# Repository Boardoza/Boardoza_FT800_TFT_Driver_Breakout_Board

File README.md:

# Boardoza FT800 TFT Driver Breakout Board

The **Boardoza FT800 TFT Driver Breakout Board** is a powerful graphics controller solution designed to simplify the creation of high-quality Human-Machine Interfaces (HMIs) for makers and embedded developers. Powered by the **Bridgetek (FTDI) FT800 Embedded Video Engine (EVE)**, this module unburdens your main microcontroller by handling complex graphics rendering, audio processing, and touch control on a dedicated chip. It is the perfect bridge for connecting low-cost MCUs to sophisticated color displays.

Operating with a **5V supply**, the board communicates via a standard **SPI interface** at speeds up to 30 MHz, making it compatible with popular platforms including Arduino, ESP32, STM32, and Raspberry Pi. It supports **WQVGA (480x272)** and **QVGA (320x240)** resolution TFT displays through a standard 40-pin FPC connector. Beyond graphics, it includes a built-in audio engine with PWM output for direct speaker connection. The FT800 offers flexible touch input options with **integrated resistive touch support** and **native capacitive touch connectivity via I²C**, providing a complete multimedia solution for industrial control panels, medical devices, IoT projects, and smart home interfaces.

## [Click here to purchase!](https://www.ozdisan.com/p/arduino-sensorleri-ve-modulleri-613/boardoza-boardoza-ft800-1473939)

|Front Side|Back Side|
|:---:|:---:|
| | |

---

## Key Features

- **Dual Resolution Support:** Compatible with WQVGA (480x272) and QVGA (320x240) TFT panels with both DE mode and VSYNC/HSYNC synchronization.  
- **Works with any MCU:** Uses standard SPI, compatible with Arduino, ESP32, STM32, Raspberry Pi Pico, and more.  
- **Resistive & Capacitive Touch Support:** Integrated resistive and capacitive touch controller support via I²C.  
- **Audio Output:** Mono audio channel with PWM output and dedicated speaker connections.  
- **Object-Oriented Architecture:** Advanced command-based system enables low-cost host MCUs to create sophisticated HMI applications.  
- **Perfect for custom HMIs:** Great for dashboards, robotics screens, measurement devices, smart panels, and DIY UI projects.  
- **Display Control Signals:** Built-in display enable, pixel clock, and sync signal outputs for direct TFT panel control.  
- **Interrupt Capability:** Hardware interrupt output for efficient event-driven programming.  

---

## FT800 vs [FT810](https://github.com/Boardoza/Boardoza_FT810_TFT_Driver_Breakout_Board) Comparison

| Feature | FT800 | [FT810](https://github.com/Boardoza/Boardoza_FT810_TFT_Driver_Breakout_Board) |
|:---|:---:|:---:|
| **Supported Resolutions** | WQVGA (480x272), QVGA (320x240) | up to SVGA (800x600) |
| **Maximum Resolution** | WQVGA (480x272) | SVGA (800x600) |
| **Resistive Touch Support** | ✓ Integrated | ✓ Integrated |
| **Capacitive Touch Support** | ✓ Direct connection via I²C (J9) | ✗ Requires expansion board |
| **Audio Output** | ✓ Mono with PWM output, integrated speaker & line out | ✓ Mono with PWM output, integrated speaker & line out |
| **SPI Interface** | ✓ Up to 30 MHz | ✓ Up to 30 MHz |
| **Board Dimensions** | 40mm x 100mm | 40mm x 100mm |

> **Note:** The FT800 provides native capacitive touch support through the dedicated I²C connector (J9), allowing direct connection to capacitive touch panels. The FT810 focuses on resistive touch integration but can support capacitive touch through an external interface board if needed.

---

## Technical Specifications

**Model:** FT800  
**Manufacturer:** Bridgetek (FTDI)  
**Input Voltage:** 5V  
**Voltage Input Type:** Multiple pin connector (standard 2.50mm pitch)  
**Working Current:** 150mA  
**Functions:** Embedded Video Engine (Graphics Controller, Audio Processor, Touch Controller)  
**Interface:** SPI (up to 30 MHz), I²C (capacitive touch)  
**Supported Resolutions:** WQVGA (480x272), QVGA (320x240)  
**Display Modes:** Data Enable (DE), VSYNC/HSYNC  
**Touch Input:** Resistive (integrated), Capacitive (external via I²C)  
**Color Depth:** RGB666 (18-bit, 6-bit per color channel)  
**Audio Output:** Mono PWM audio channel  
**Connector Type:** 40-Pin FPC  
**Operating Temperature:** -40°C ~ +85°C  
**Board Dimensions:** 40mm x 100mm

---

## Board Pinout

### **( J1 ) Power and Control**

| Pin Number | Pin Name | Description |
|:---:|:---:|---|
| 1 | 3V3 | 3.3V Voltage Output |
| 2 | 5V | Board Supply Input |
| 3 | GND | Ground |
| 4 | PD | Power Down / Board Enable (Active High, 3.3V-5V compatible) |
| 5 | INT | Interrupt Output (3.3V logic level) |

### **( J2 ) TFT Display & Touch Interface**

| Pin Number | Pin Name | Description |
|:---:|:---:|---|
| 1 | LED- | LED Backlight Driver Negative |
| 2 | LED+ | LED Backlight Driver Positive |
| 3 | GND | Ground |
| 4 | VDD | 3.3V Power Output |
| 5 | GND | Ground |
| 6 | GND | Ground |
| 7 | R2 | Red RGB Signal Bit 2 |
| 8 | R3 | Red RGB Signal Bit 3 |
| 9 | R4 | Red RGB Signal Bit 4 |
| 10 | R5 | Red RGB Signal Bit 5 |
| 11 | R6 | Red RGB Signal Bit 6 |
| 12 | R7 | Red RGB Signal Bit 7 |
| 13 | GND | Ground |
| 14 | GND | Ground |
| 15 | G2 | Green RGB Signal Bit 2 |
| 16 | G3 | Green RGB Signal Bit 3 |
| 17 | G4 | Green RGB Signal Bit 4 |
| 18 | G5 | Green RGB Signal Bit 5 |
| 19 | G6 | Green RGB Signal Bit 6 |
| 20 | G7 | Green RGB Signal Bit 7 |
| 21 | GND | Ground |
| 22 | GND | Ground |
| 23 | B2 | Blue RGB Signal Bit 2 |
| 24 | B3 | Blue RGB Signal Bit 3 |
| 25 | B4 | Blue RGB Signal Bit 4 |
| 26 | B5 | Blue RGB Signal Bit 5 |
| 27 | B6 | Blue RGB Signal Bit 6 |
| 28 | B7 | Blue RGB Signal Bit 7 |
| 29 | GND | Ground |
| 30 | DATA_CLOCK | TFT Pixel Clock Output (Push-Pull) |
| 31 | DISP | Display Enable Output (Push-Pull) |
| 32 | HSYNC | Horizontal Sync Output (Push-Pull) |
| 33 | VSYNC | Vertical Sync Output (Push-Pull) |
| 34 | DE | Data Enable Output (Push-Pull) |
| 35 | NC | Not Connected |
| 36 | GND | Ground |
| 37 | X+ | Touch Screen Right Electrode |
| 38 | Y- | Touch Screen Bottom Electrode |
| 39 | X- | Touch Screen Left Electrode |
| 40 | Y+ | Touch Screen Top Electrode |

### **( J3 ) Speaker Output**

| Pin Number | Pin Name | Description |
|:---:|:---:|---|
| 1 | Speaker+ | Speaker Output Positive |
| 2 | Speaker- | Speaker Output Negative |

### **( J5 ) Audio Line Output**

| Pin Number | Pin Name | Description |
|:---:|:---:|---|
| 1 | Audio Out+ | Audio Line Output Positive |
| 2 | Audio Out- | Audio Line Output Negative |

### **( J6 ) SPI Communication**

| Pin Number | Pin Name | Description |
|:---:|:---:|---|
| 1 | CS | SPI Chip Select (Active Low) |
| 2 | MISO | SPI Master In, Slave Out |
| 3 | MOSI | SPI Master Out, Slave In |
| 4 | SCK | SPI Clock Input |

### **( J7 ) Auxiliary Power**

| Pin Number | Pin Name | Description |
|:---:|:---:|---|
| 1 | 5V+ | Board Supply Input |
| 2 | 5V- | Ground |

### **( J9 ) Capacitive Touch I²C Interface**

| Pin Number | Pin Name | Description |
|:---:|:---:|---|
| 1 | INT | Capacitive Touch Interrupt (Active Low) |
| 2 | SDA | I²C Serial Data Pin |
| 3 | SCL | I²C Serial Clock Pin |
| 4 | RST | Capacitive Touch Reset (Active Low) |

> **Note:** The FT800 includes an integrated resistive touch controller. The J9 connector provides optional support for external capacitive touch controllers via I²C interface.

---

## Board Dimensions

---

## Step Files

[Boardoza FT800.step](./assets/FT800%20Step.step)

---

## Datasheet

[FTDI FT800 Datasheet.pdf](./assets/FT800%20Datasheet.pdf)

---

## Version History

- V1.0.0 – Initial Release  

---

## Support

For technical questions or assistance, please contact **<support@boardoza.com>**

---

## License

Shield: [![CC BY-SA 4.0][cc-by-sa-shield]][cc-by-sa]

This work is licensed under a [Creative Commons Attribution-ShareAlike 4.0 International License][cc-by-sa].

[![CC BY-SA 4.0][cc-by-sa-image]][cc-by-sa]

[cc-by-sa]: http://creativecommons.org/licenses/by-sa/4.0/
[cc-by-sa-image]: https://licensebuttons.net/l/by-sa/4.0/88x31.png
[cc-by-sa-shield]: https://img.shields.io/badge/License-CC%20BY--SA%204.0-lightgrey.svg

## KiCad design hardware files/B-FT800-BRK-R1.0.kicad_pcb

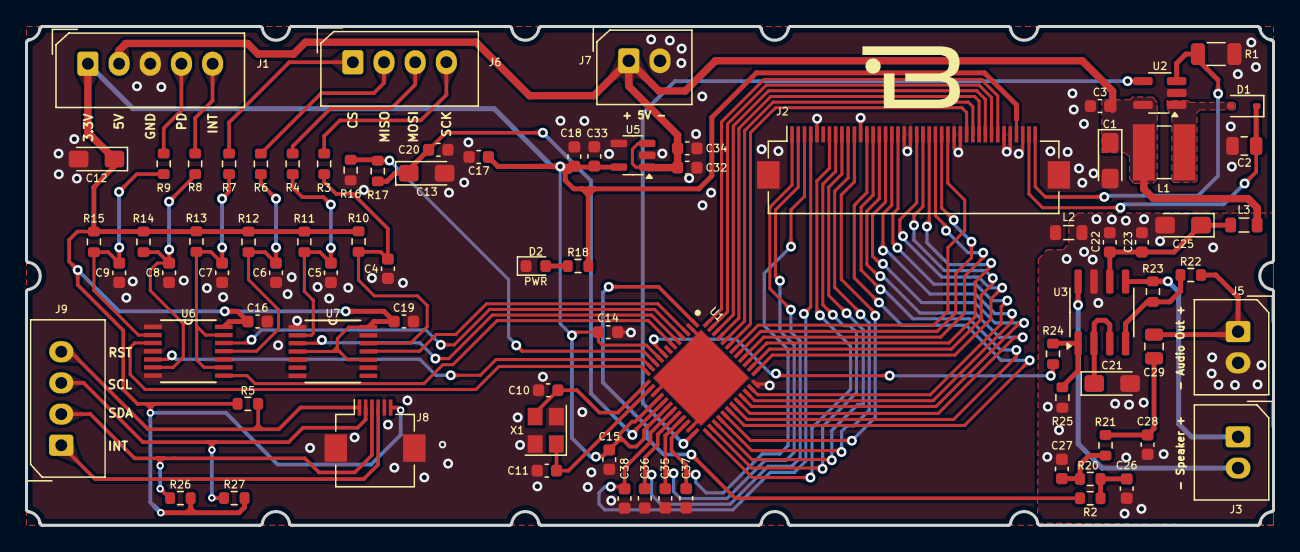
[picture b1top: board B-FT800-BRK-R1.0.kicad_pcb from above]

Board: 2 copper layers, 100.0 x 40.0 mm, 81 parts (0 on the bottom side), 74 nets.

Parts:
C1: 1uF 35V A tantal; CP_EIA-3216-18_Kemet-A_Pad1.58x1.35mm_HandSolder
C2: 220nF; C_0805_2012Metric
C3, C14, C15, C16, C17, C18, C19, C20, C23, C34: 100nF; C_0603_1608Metric
C4, C5, C6, C7, C8, C9: 10pF; C_0603_1608Metric
C10, C11: 27pF; C_0603_1608Metric
C12, C13, C21, C25: 4,7uF 10V A tantal; CP_EIA-3216-18_Kemet-A_Pad1.58x1.35mm_HandSolder
C22: 10nF; C_0603_1608Metric
C26, C27, C28: 4,7nF; C_0603_1608Metric
C29: 330nF; C_0805_2012Metric
C32, C33: 1uF; C_0603_1608Metric
C35, C36, C37, C38: 3,3nF; C_0603_1608Metric
D1: SS0840WS_R1_00001; D_SOD-323
D2: RED; LED_0603_1608Metric
J1: Conn_01x05; 2317-05S_1x05_P2.50mm_Vertical
J2: Conn_01x40; Hirose_FH12-40S-0.5SH_1x40-1MP_P0.50mm_Horizontal
J3, J5, J7: Conn_01x02; 2317-02S_1x02_P2.50mm_Vertical
J6, J9: Conn_01x04; 2317-04S_1x04_P2.50mm_Vertical
J8: Conn_01x06; Hirose_FH12-6S-0.5SH_1x06-1MP_P0.50mm_Horizontal
L1: PCD0403MT100; L_Ferrocore_DLG-0403
L2, L3: LCB2012-601Y-N; L_0805_2012Metric
R1: 2R2; R_1206_3216Metric
R2, R20, R21: 1K; R_0603_1608Metric
R3, R4, R6, R7, R8, R9, R24: 33R; R_0603_1608Metric
R5, R22, R26, R27: 10K; R_0603_1608Metric
R10, R11, R12, R13, R14, R15, R16, R25: 47K; R_0603_1608Metric
R17: NC; R_0603_1608Metric
R18: 330R; R_0603_1608Metric
R23: 20K; R_0603_1608Metric
U1: FT800Q-R; QFN50P700X700X100-49N-D
U2: MIC2287CYD5-TR; SOT-23-5_HandSoldering
U3: AP4890; SOIC-8_3.9x4.9mm_P1.27mm
U5: TLV70033DDCR; SOT-23-5
U6, U7: MC74LCX125DTR2G; SOP65P640X120-14N
X1: RH100-12.000-18-2020-TR; Crystal_SMD_3225-4Pin_3.2x2.5mm

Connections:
/Connectors/AGND: C21.2, C22.1, C23.1, C25.2, C26.2, C27.1, C28.1, J5.2, L2.1, R25.1, U3.7 (GND)
/Connectors/INTC: J8.3, J9.1
/Connectors/RST: J8.6, J9.4, R5.1
/Connectors/SCL: J8.5, J9.3, R27.1
/Connectors/SDA: J8.4, J9.2, R26.1
/LED_OUT: D1.2 (A), L1.2, U2.1 (VOUT)
AUDIO: R2.2, U1.1 (AUDIO_L)
AUDIO_SHDN: R24.1, U1.8 (GPIO1)
B2: J2.23, U1.35 (B2)
B3: J2.24, U1.34 (B3)
B4: J2.25, U1.33 (B4)
B5: J2.26, U1.32 (B5)
B6: J2.27, U1.31 (B6)
B7: J2.28, U1.30 (B7)
BLIGHT: U1.24 (BACKLIGHT), U2.4 (EN)
CS: C7.2, R7.1, R13.2, U6.9 (A3), U6.13 (~OE2)
DATA_CLOCK: J2.30, U1.29 (PCLK)
DE: J2.34, U1.25 (DE)
DISP: J2.31, U1.28 (DISP)
FT_CS: U1.6 (CS_N/_I2C_SA1), U6.8 (O3)
FT_INT: U1.11 (INT_N), U6.5 (A1)
FT_MISO: U1.4 (MISO/_I2C_SDA), U6.12 (A2)
FT_MOSI: U1.5 (MOSI/_I2C_SA0), U7.3 (O0)
FT_PD: U1.12 (PD_N), U6.3 (O0)
FT_SCK: U1.3 (SPI_SCLK/_I2C_SCL), U7.11 (O2)
G2: J2.15, U1.42 (G2)
G3: J2.16, U1.41 (G3)
G4: J2.17, U1.40 (G4)
G5: J2.18, U1.39 (G5)
G6: J2.19, U1.38 (G6)
G7: J2.20, U1.37 (G7)
GND: C1.2, C2.2, C3.1, C4.1, C5.1, C6.1, C7.1, C8.1, C9.1, C10.1, C11.2, C12.2, C13.2, C14.2, C15.2, C16.2, C17.2, C18.2, C19.2, C20.2, C32.2, C33.2, C34.2, C35.1, C36.2, C37.1, C38.1, D2.1 (K), J1.3, J2.3, J2.5, J2.6, J2.13, J2.14, J2.21, J2.22, J2.29, J2.36, J2.41, J2.42, J7.2, J8.2, J8.MP, L2.2, R1.1, R16.2, U1.2 (GND_1), U1.15 (GND_2), U1.23 (GND_3), U1.36 (GND_4), U1.49 (GND_5), U2.2 (GND), U5.2 (GND), U5.4 (BP), U6.1 (~OE0), U6.4 (~OE1), U6.7 (GND), U6.10 (~OE3), U7.1 (~OE0), U7.5 (A1), U7.7 (GND), U7.9 (A3), U7.13 (~OE2), X1.2, X1.4
HSYNC: J2.32, U1.27 (HSYNC)
INT: C8.2, R8.1, R14.2, U6.6 (O1)
LED+: C2.1, D1.1 (K), J2.2
LED-: J2.1, R1.2, U2.3 (FB)
MISO: C6.2, R6.1, R12.1, U6.11 (O2)
MOSI: C5.2, R4.1, R11.1, U7.2 (A0)
unnamed: C26.1, R2.1, R20.2
unnamed: C27.2, R20.1, R21.2
unnamed: C28.2, C29.1, R21.1
unnamed: D2.2 (A), R18.1
unnamed: J1.4, R9.2
unnamed: J1.5, R8.2
unnamed: J3.1, R23.1, U3.5 (OUT+)
unnamed: J3.2, U3.8 (OUT-)
unnamed: C29.2, J5.1, R22.1
unnamed: J6.1, R7.2
unnamed: J6.2, R6.2
unnamed: J6.3, R4.2
unnamed: J6.4, R3.2
unnamed: R16.1, R17.2, U1.10 (MODE)
unnamed: C21.1, U3.2 (BYPASS), U3.3 (IN+)
unnamed: R22.2, R23.2, U3.4 (IN-)
unnamed: C22.2, C23.2, C25.1, L3.1, U3.6 (VDD)
unnamed: R24.2, R25.2, U3.1 (~SD)
OSC_IN: C10.2, U1.13 (X1/_CLK), X1.3
OSC_OUT: C11.1, U1.14 (X2), X1.1
PD: C9.2, R9.1, R15.2, U6.2 (A0)
R2: J2.7, U1.48 (R2)
R3: J2.8, U1.47 (R3)
R4: J2.9, U1.46 (R4)
R5: J2.10, U1.45 (R5)
R6: J2.11, U1.44 (R6)
R7: J2.12, U1.43 (R7)
SCK: C4.2, R3.1, R10.1, U7.12 (A2)
VDD: C12.1, C14.1, C15.1, C16.1, C17.1, C18.1, C19.1, C33.1, J1.1, J2.4, J8.1, R5.2, R10.2, R11.2, R12.2, R13.1, R14.1, R15.1, R18.2, R26.2, R27.2, U1.9 (VCCIO), U1.16 (VCC_1), U1.18 (VCC_2), U5.5 (OUT), U6.14 (VCC), U7.4 (~OE1), U7.10 (~OE3), U7.14 (VCC)
VDD_BL: C1.1, C3.2, C32.1, C34.1, J1.2, J7.1, L1.1, L3.2, U2.5 (VBAT), U5.1 (IN), U5.3 (EN)
VDD_Core: C13.1, C20.1, R17.1, U1.17 (VCC1V2)
VSYNC: J2.33, U1.26 (VSYNC)
X+: C38.2, J2.37, U1.19 (X+)
X-: C35.2, J2.39, U1.21 (X-)
Y+: C36.1, J2.40, U1.20 (Y+)
Y-: C37.2, J2.38, U1.22 (Y-)
